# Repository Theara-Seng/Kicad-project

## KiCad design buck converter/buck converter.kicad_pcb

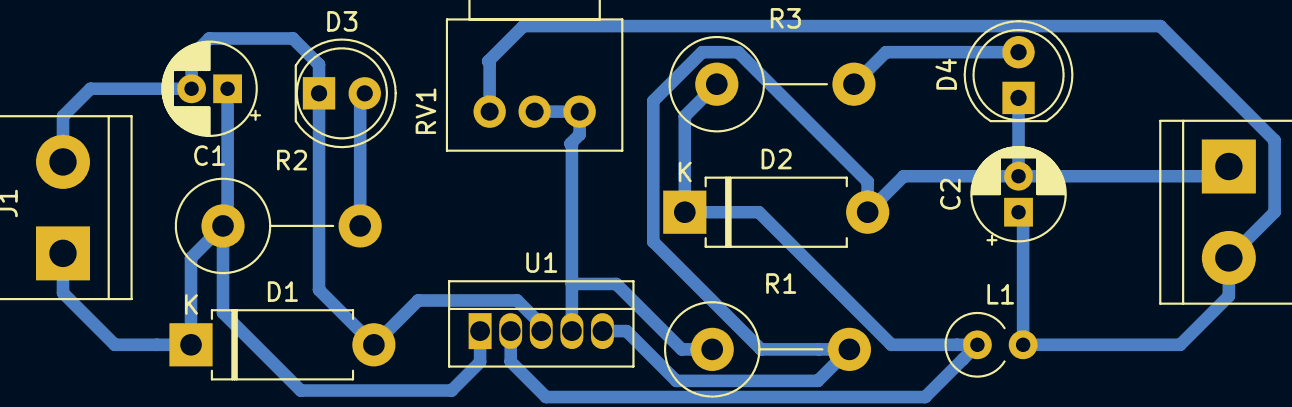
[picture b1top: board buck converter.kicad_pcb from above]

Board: 2 copper layers, 14 parts (0 on the bottom side), 7 nets.

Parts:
C1, C2: 220uF; CP_Radial_D5.0mm_P2.00mm
D1, D2: D_Schottky; D_DO-15_P10.16mm_Horizontal
D3, D4: LED; LED_D5.0mm
J1: Input; TerminalBlock_bornier-2_P5.08mm
J2: Output; TerminalBlock_bornier-2_P5.08mm
L1: L; L_Axial_L7.0mm_D3.3mm_P2.54mm_Vertical_Fastron_MICC
R1: 470; R_Axial_DIN0516_L15.5mm_D5.0mm_P7.62mm_Vertical
R2, R3: 1k; R_Axial_DIN0516_L15.5mm_D5.0mm_P7.62mm_Vertical
RV1: 10K; Potentiometer_Alps_RK097_Single_Horizontal
U1: LM2596S-ADJ; TO-262-5_Vertical

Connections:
GND: C1.2, C2.2, D1.2, D2.2, D3.1, D4.1, J1.2, J2.1, R1.2, U1.3, U1.5
unnamed: C1.1, D1.1, J1.1, R2.1, U1.1
unnamed: C2.1, J2.2, L1.2, RV1.3
unnamed: D2.1, L1.1, R3.1, U1.2
unnamed: D3.2, R2.2
unnamed: D4.2, R3.2
unnamed: R1.1, RV1.1, RV1.2, U1.4

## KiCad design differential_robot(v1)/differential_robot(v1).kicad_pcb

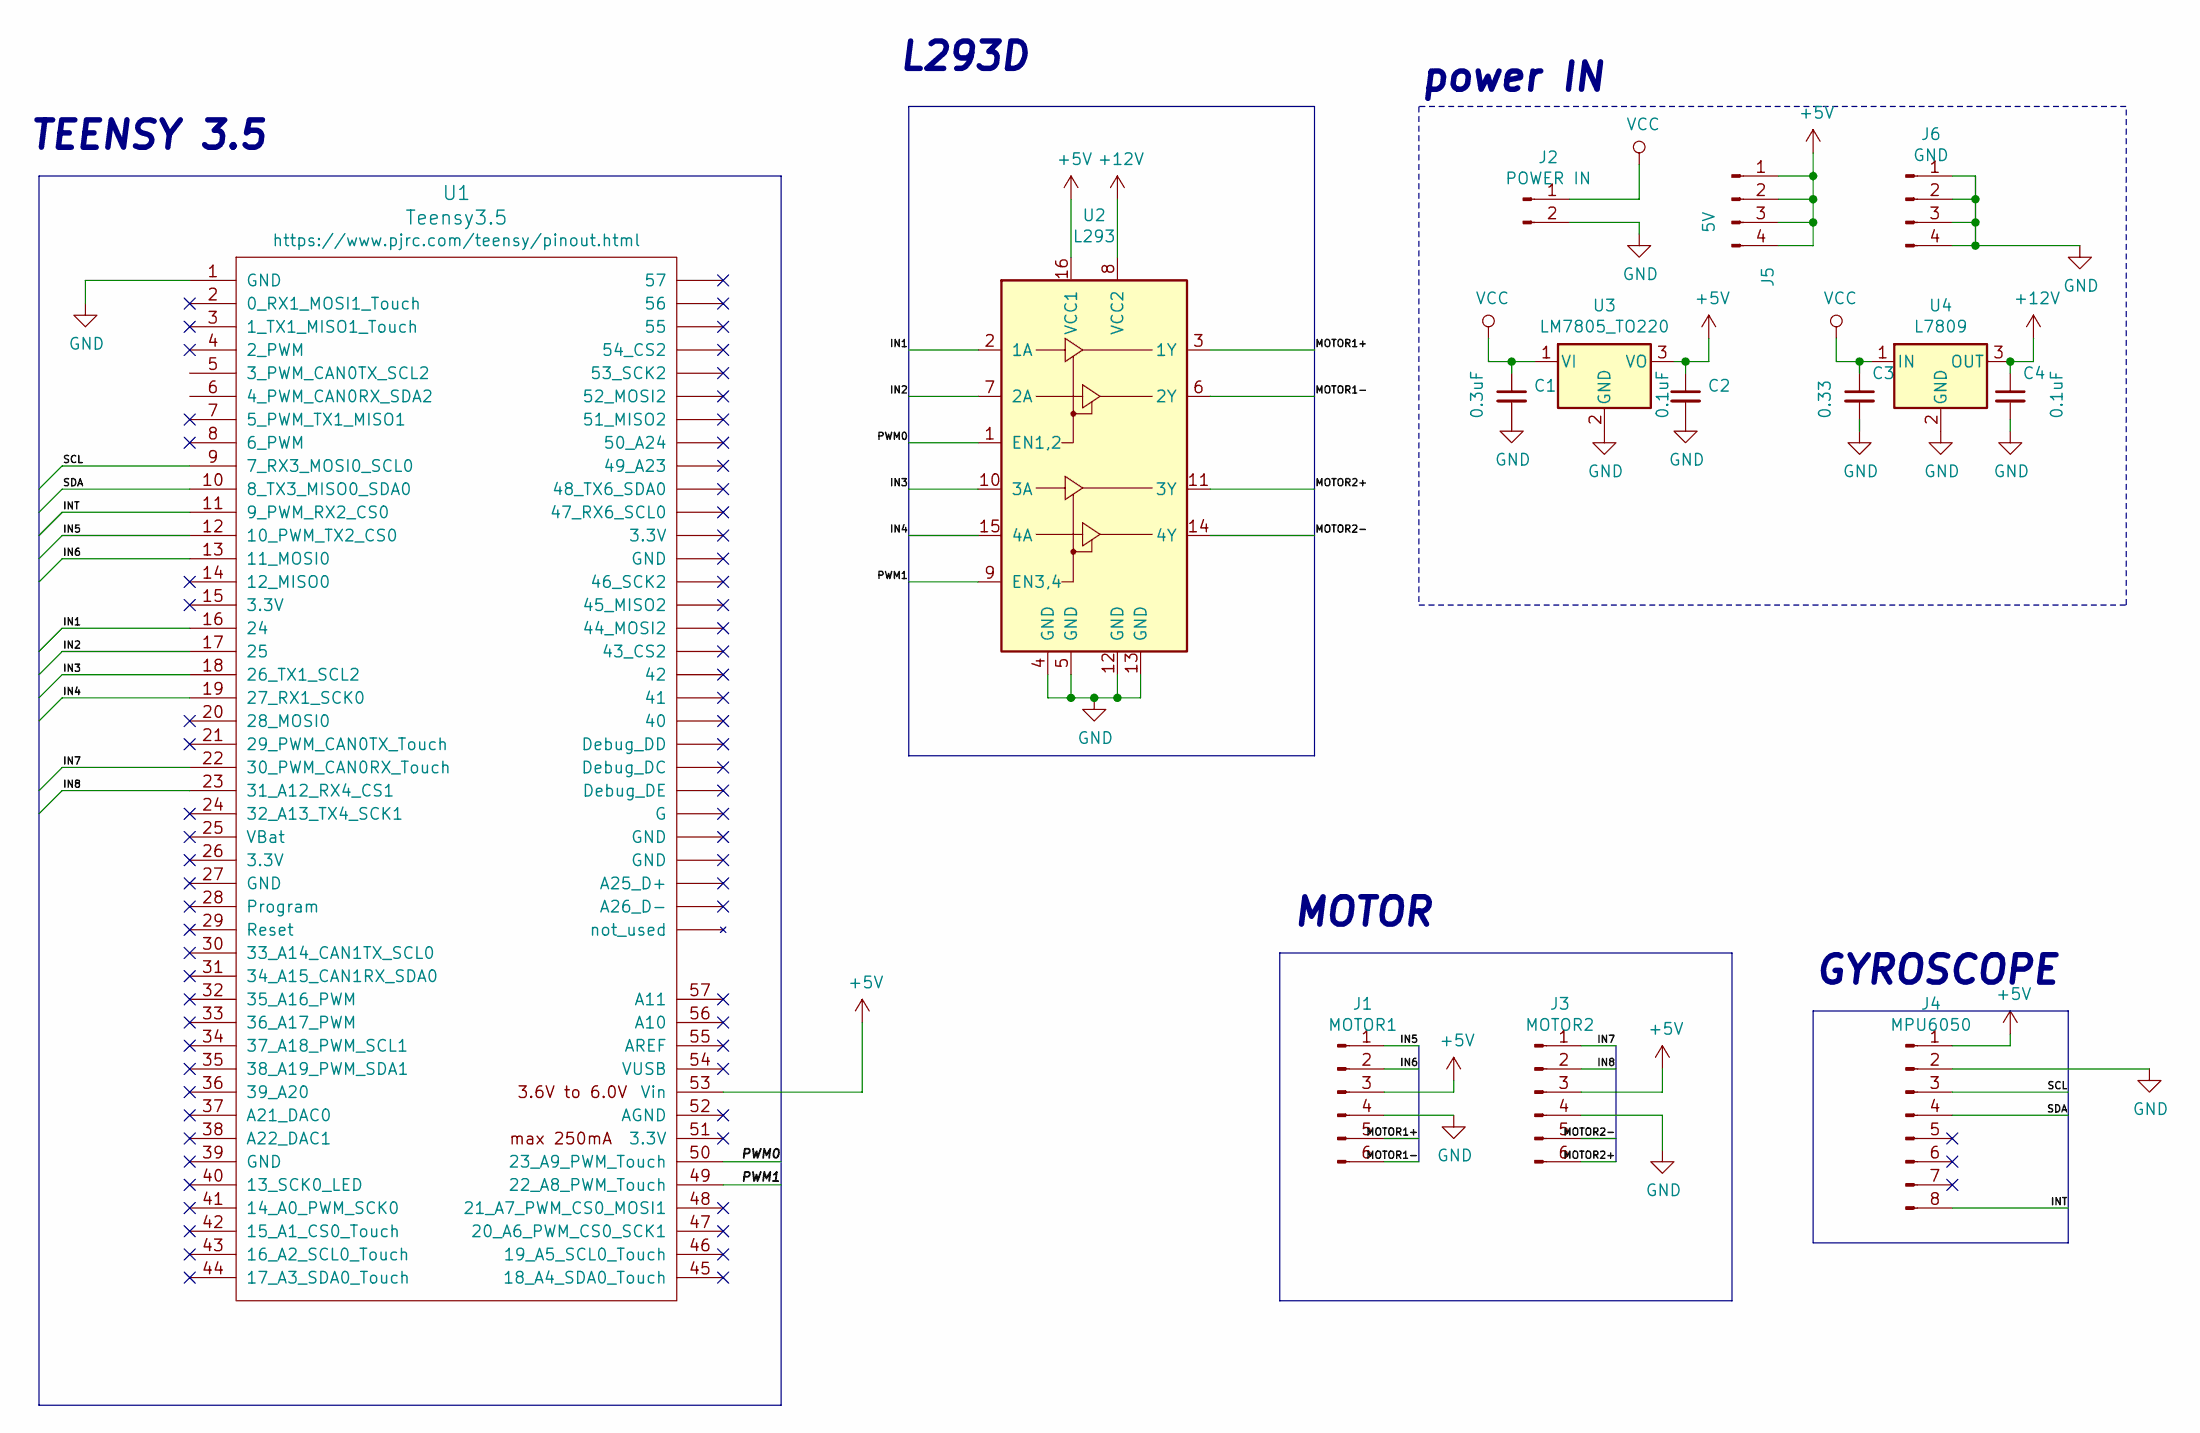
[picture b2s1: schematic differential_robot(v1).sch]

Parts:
C1: 0.3uF; CP_Radial_Tantal_D4.5mm_P2.50mm
C2, C4: 0.1uF; CP_Radial_Tantal_D4.5mm_P2.50mm
C3: 0.33; CP_Radial_Tantal_D4.5mm_P2.50mm
J1: MOTOR1; PinSocket_1x06_P2.54mm_Vertical
J2: POWER IN; TerminalBlock_bornier-2_P5.08mm
J3: MOTOR2; PinSocket_1x06_P2.54mm_Vertical
J4: MPU6050; PinSocket_1x08_P2.54mm_Vertical
J5: 5V; PinSocket_1x04_P2.54mm_Vertical
J6: GND; PinSocket_1x04_P2.54mm_Vertical
U1: Teensy3.5; Teensy35_36
U2: L293; DIP-16_W7.62mm
U3: LM7805_TO220; TO220
U4: L7809; TO220

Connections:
+5V: C2.1, J1.3, J3.3, J4.1, J5.1, J5.2, J5.3, J5.4, U1.53 (Vin), U2.16 (VCC1), U3.3 (VO)
+12V: C4.1, U2.8 (VCC2), U4.3 (OUT)
/IN1: U1.16 (24), U2.2 (1A)
/IN2: U1.17 (25), U2.7 (2A)
/IN3: U1.18 (26_TX1_SCL2), U2.10 (3A)
/IN4: U1.19 (27_RX1_SCK0), U2.15 (4A)
/IN5: J1.1, U1.12 (10_PWM_TX2_CS0)
/IN6: J1.2, U1.13 (11_MOSI0)
/IN7: J3.1, U1.22 (30_PWM_CAN0RX_Touch)
/IN8: J3.2, U1.23 (31_A12_RX4_CS1)
/INT: J4.8, U1.11 (9_PWM_RX2_CS0)
/MOTOR1+: J1.5, U2.3 (1Y)
/MOTOR1-: J1.6, U2.6 (2Y)
/MOTOR2+: J3.6, U2.11 (3Y)
/MOTOR2-: J3.5, U2.14 (4Y)
/PWM0: U1.50 (23_A9_PWM_Touch), U2.1 (EN1,2)
/PWM1: U1.49 (22_A8_PWM_Touch), U2.9 (EN3,4)
/SCL: J4.3, U1.9 (7_RX3_MOSI0_SCL0)
/SDA: J4.4, U1.10 (8_TX3_MISO0_SDA0)
GND: C1.2, C2.2, C3.2, C4.2, J1.4, J2.2, J3.4, J4.2, J6.1, J6.2, J6.3, J6.4, U1.1 (GND), U2.4 (GND), U2.5 (GND), U2.12 (GND), U2.13 (GND), U3.2 (GND), U4.2 (GND)
VCC: C1.1, C3.1, J2.1, U3.1 (VI), U4.1 (IN)

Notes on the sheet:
power IN
MOTOR
GYROSCOPE
L293D
TEENSY 3.5

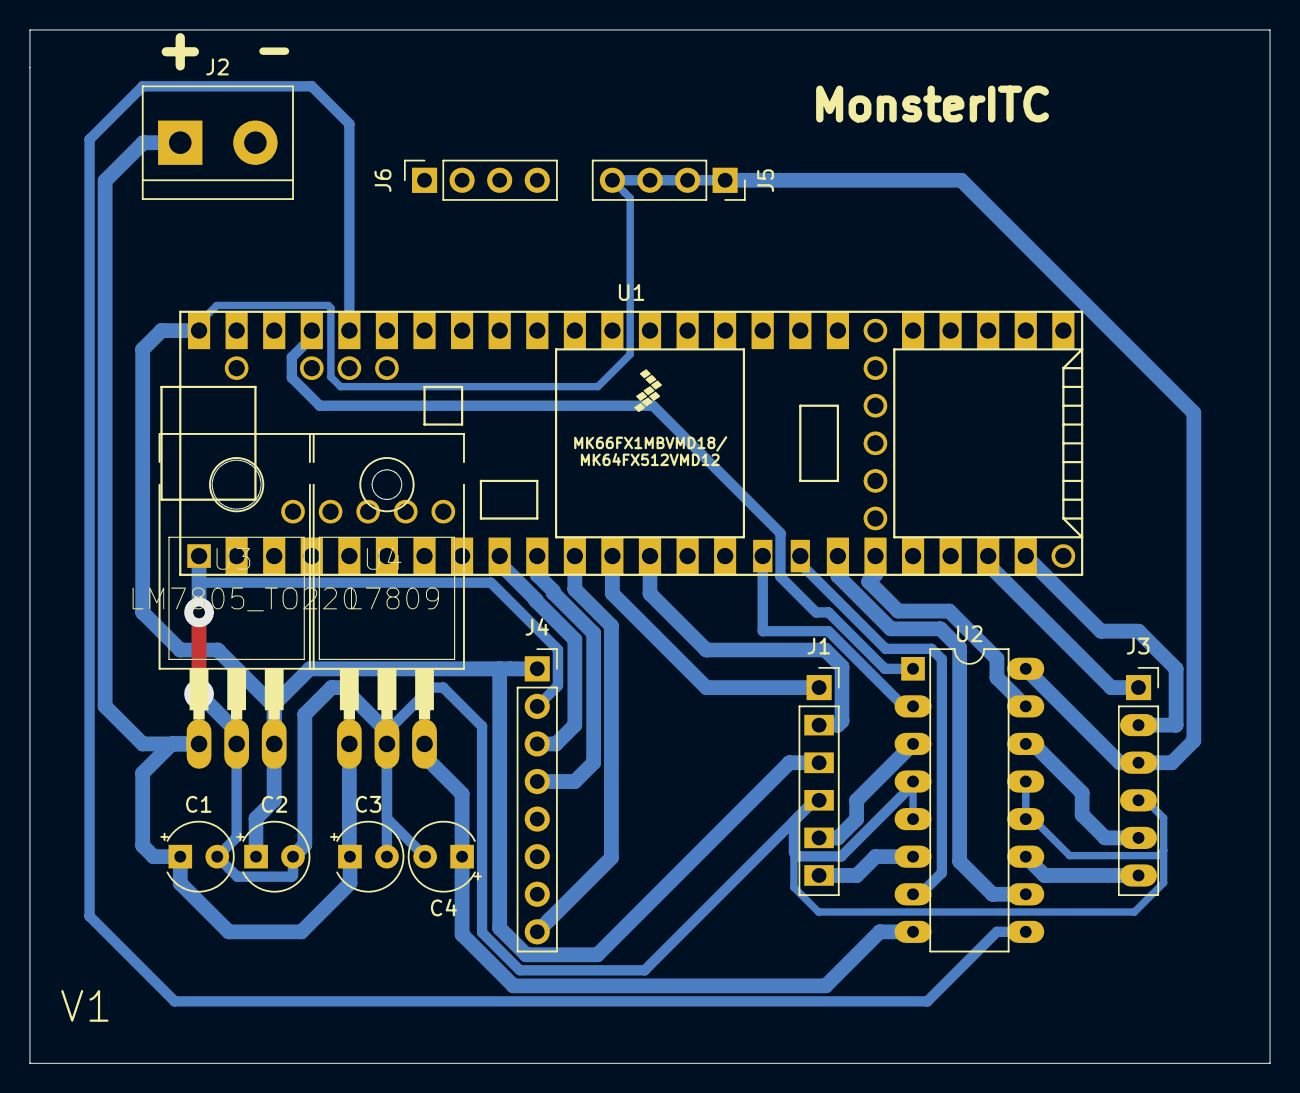
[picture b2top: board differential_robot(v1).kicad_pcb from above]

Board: 2 copper layers, 83.8 x 69.8 mm, 14 parts (0 on the bottom side), 21 nets.

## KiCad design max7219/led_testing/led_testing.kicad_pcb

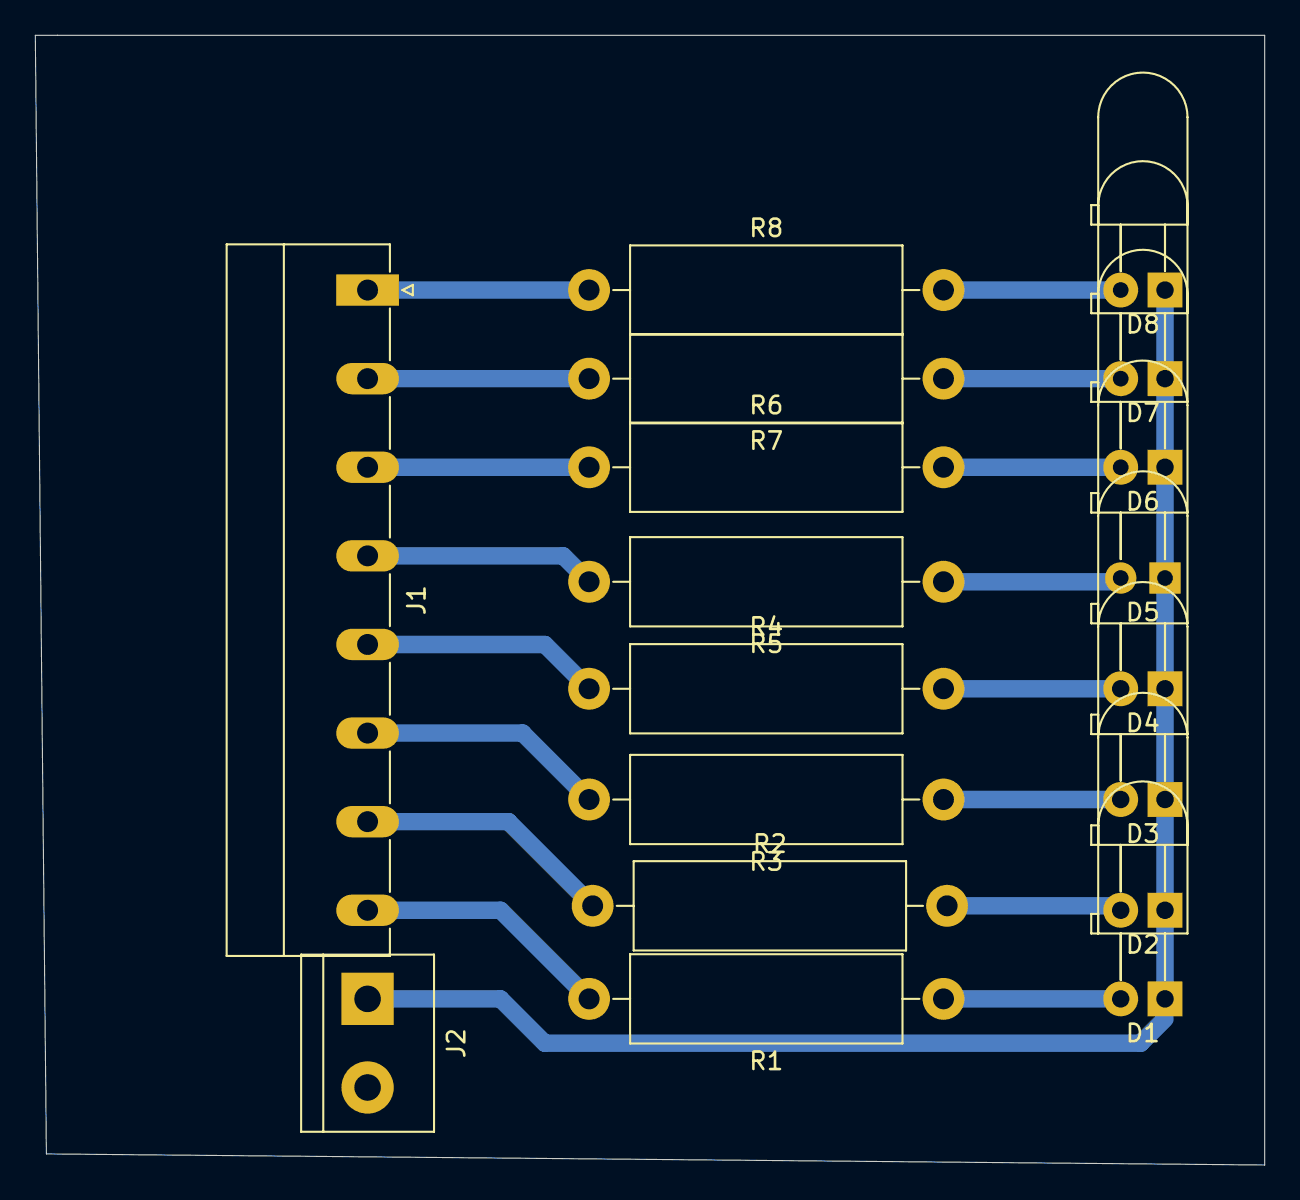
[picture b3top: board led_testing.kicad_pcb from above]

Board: 2 copper layers, 70.5 x 64.8 mm, 18 parts (0 on the bottom side), 17 nets.

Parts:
D1, D2, D3, D4, D5, D6, D7, D8: LED; LED_D5.0mm_Horizontal_O3.81mm_Z15.0mm
J1: Conn_01x08_Female; PhoenixContact_MC-G_08x5.08mm_Angled
J2: Conn_01x01_Female; TerminalBlock_bornier-2_P5.08mm
R1, R2, R3, R4, R5, R6, R7, R8: R; R_Axial_DIN0516_L15.5mm_D5.0mm_P20.32mm_Horizontal

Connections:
/GND: D1.1, D2.1, D3.1, D4.1, D5.1, D6.1, D7.1, D8.1, J2.1
/PB0: J1.8, R1.2
/PB1: J1.7, R2.1
/PB2: J1.6, R3.2
/PB3: J1.5, R4.1
/PB4: J1.4, R5.2
/PB5: J1.3, R6.1
/PB6: J1.2, R7.2
/PB7: J1.1, R8.1
unnamed: D1.2, R1.1
unnamed: D2.2, R2.2
unnamed: D3.2, R3.1
unnamed: D4.2, R4.2
unnamed: D5.2, R5.1
unnamed: D6.2, R6.2
unnamed: D7.2, R7.1
unnamed: D8.2, R8.2

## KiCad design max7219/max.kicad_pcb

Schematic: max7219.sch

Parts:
C1: C; CP_Radial_D13.0mm_P5.00mm
C2: C; CP_Radial_D14.0mm_P5.00mm
D1, D2, D3, D4, D5, D6, D7, D8, D9, D10, D11, D12, D13, D14, D15, D16, D17, D18, D19, D20, D21, D22, D23, D24, D25, D26, D27, D28, D29, D30, D31, D32, D33, D34, D35, D36, D37, D38, D39, D40, D41, D42, D43, D44, D45, D46, D47, D48, D49, D50, D51, D52, D53, D54, D55, D56, D57, D58, D59, D60, D61, D62, D63, D64: LED; LED_D3.0mm_Horizontal_O1.27mm_Z2.0mm
J1: Conn_01x05_Female; TerminalBlock_bornier-5_P5.08mm
R1: R; R_Axial_DIN0614_L14.3mm_D5.7mm_P15.24mm_Horizontal
U1: MAX7219; DIL24

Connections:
CLK: J1.2, U1.13
DIG0: D1.1 (K), D9.1 (K), D17.1 (K), D25.1 (K), D33.1 (K), D41.1 (K), D49.1 (K), D57.1 (K), U1.2
DIG1: D2.1 (K), D10.1 (K), D18.1 (K), D26.1 (K), D34.1 (K), D42.1 (K), D50.1 (K), D58.1 (K), U1.11
DIG2: D3.1 (K), D11.1 (K), D19.1 (K), D27.1 (K), D35.1 (K), D43.1 (K), D51.1 (K), D59.1 (K), U1.6
DIG3: D4.1 (K), D12.1 (K), D20.1 (K), D28.1 (K), D36.1 (K), D44.1 (K), D52.1 (K), D60.1 (K), U1.7
DIG4: D5.1 (K), D13.1 (K), D21.1 (K), D29.1 (K), D37.1 (K), D45.1 (K), D53.1 (K), D61.1 (K), U1.3
DIG5: D6.1 (K), D14.1 (K), D22.1 (K), D30.1 (K), D38.1 (K), D46.1 (K), D54.1 (K), D62.1 (K), U1.10
DIG6: D7.1 (K), D15.1 (K), D23.1 (K), D31.1 (K), D39.1 (K), D47.1 (K), D55.1 (K), D63.1 (K), U1.5
DIG7: D8.1 (K), D16.1 (K), D24.1 (K), D32.1 (K), D40.1 (K), D48.1 (K), D56.1 (K), D64.1 (K), U1.8
DIN: J1.4, U1.1
GND: C1.1, C2.1, J1.1, U1.4, U1.9
LOAD: J1.3, U1.12
unnamed: R1.2, U1.18
SEGA: D9.2 (A), D10.2 (A), D11.2 (A), D12.2 (A), D13.2 (A), D14.2 (A), D15.2 (A), D16.2 (A), U1.14
SEGB: D17.2 (A), D18.2 (A), D19.2 (A), D20.2 (A), D21.2 (A), D22.2 (A), D23.2 (A), D24.2 (A), U1.16
SEGC: D25.2 (A), D26.2 (A), D27.2 (A), D28.2 (A), D29.2 (A), D30.2 (A), D31.2 (A), D32.2 (A), U1.20
SEGD: D33.2 (A), D34.2 (A), D35.2 (A), D36.2 (A), D37.2 (A), D38.2 (A), D39.2 (A), D40.2 (A), U1.23
SEGDP: D1.2 (A), D2.2 (A), D3.2 (A), D4.2 (A), D5.2 (A), D6.2 (A), D7.2 (A), D8.2 (A), U1.22
SEGE: D41.2 (A), D42.2 (A), D43.2 (A), D44.2 (A), D45.2 (A), D46.2 (A), D47.2 (A), D48.2 (A), U1.21
SEGF: D49.2 (A), D50.2 (A), D51.2 (A), D52.2 (A), D53.2 (A), D54.2 (A), D55.2 (A), D56.2 (A), U1.15
SEGG: D57.2 (A), D58.2 (A), D59.2 (A), D60.2 (A), D61.2 (A), D62.2 (A), D63.2 (A), D64.2 (A), U1.17
VCC: C1.2, C2.2, J1.5, R1.1, U1.19

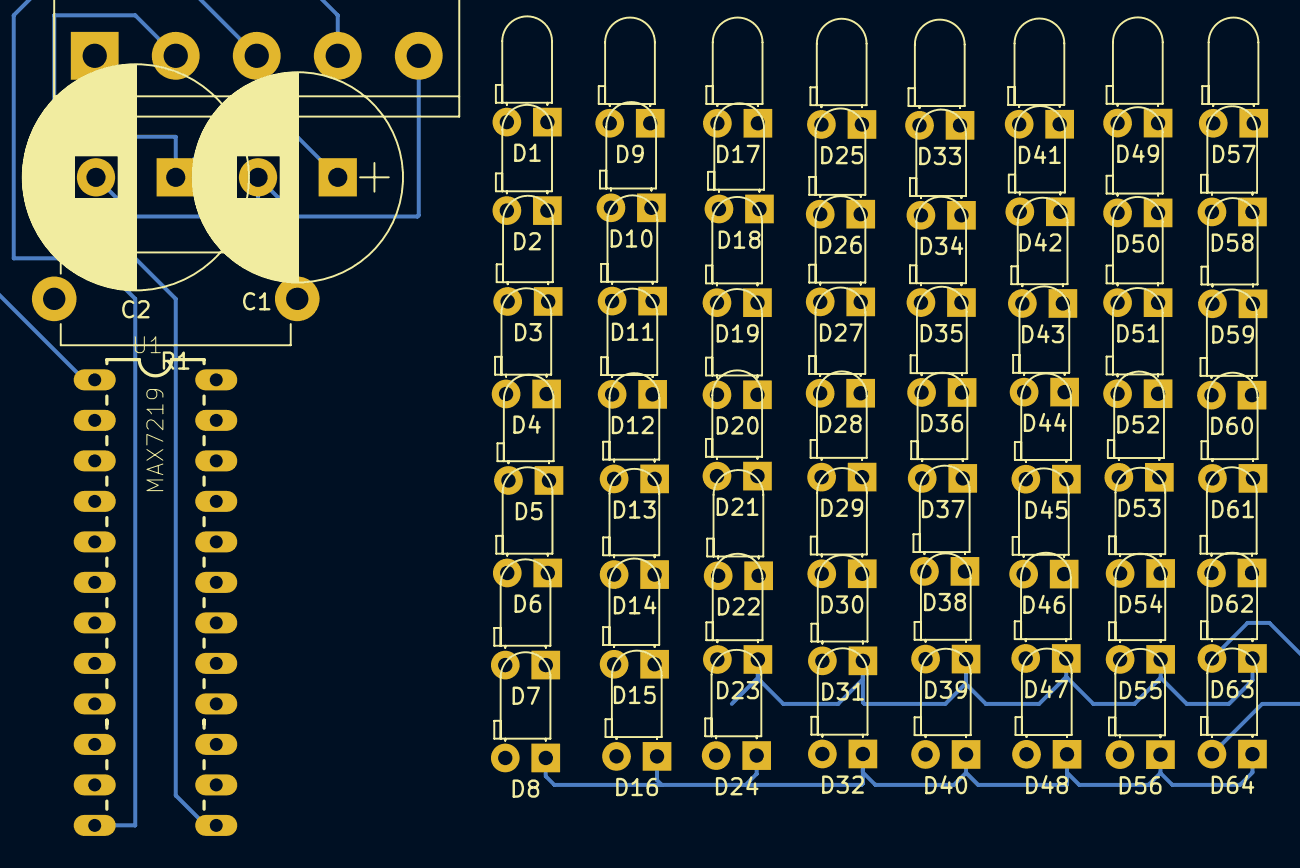
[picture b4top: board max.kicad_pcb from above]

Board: 2 copper layers, 69 parts (0 on the bottom side), 22 nets.

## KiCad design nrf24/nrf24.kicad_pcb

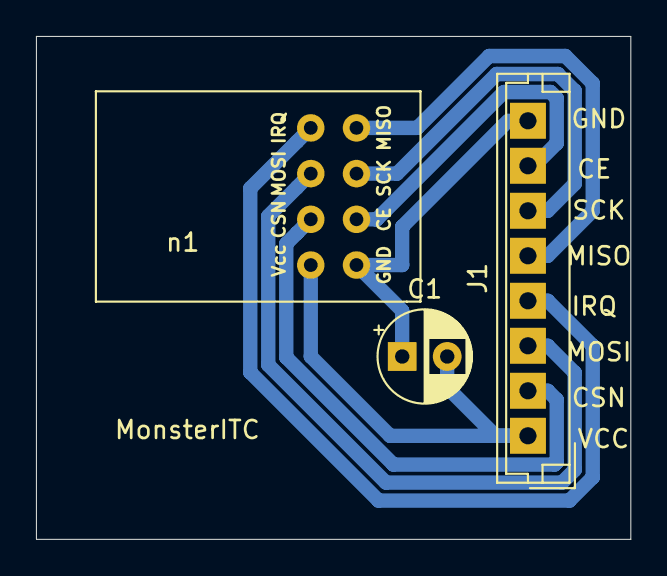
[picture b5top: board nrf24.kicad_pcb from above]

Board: 2 copper layers, 33.0 x 27.9 mm, 3 parts (0 on the bottom side), 8 nets.

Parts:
C1: C; CP_Radial_D5.0mm_P2.50mm
J1: C; JST_EH_B8B-EH-A_1x08_P2.50mm_Vertical
n1: nrf24

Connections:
unnamed: C1.1, J1.8, n1.0
unnamed: C1.2, J1.1, n1.7
unnamed: J1.2, n1.6
unnamed: J1.3, n1.5
unnamed: J1.4, n1.4
unnamed: J1.5, n1.3
unnamed: J1.6, n1.2
unnamed: J1.7, n1.1

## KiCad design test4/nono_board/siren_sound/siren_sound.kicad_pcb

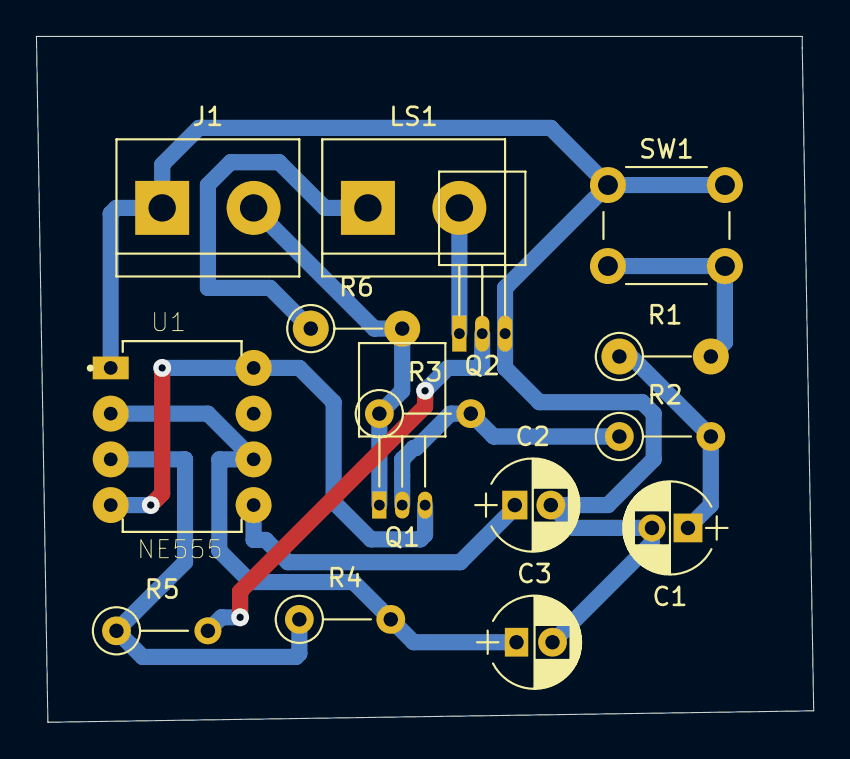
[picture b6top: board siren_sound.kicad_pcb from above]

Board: 2 copper layers, 43.2 x 38.1 mm, 15 parts (0 on the bottom side), 12 nets.

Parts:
C1, C2, C3: C; CP_Radial_D5.0mm_P2.00mm
J1: Conn_01x02_Female; TerminalBlock_bornier-2_P5.08mm
LS1: Speaker; TerminalBlock_bornier-2_P5.08mm
Q1, Q2: BC546; TO-92_Horizontal2_Inline_Narrow_Oval
R1, R2, R3, R4, R5, R6: R; R_Axial_DIN0207_L6.3mm_D2.5mm_P5.08mm_Vertical
SW1: SW_Push_Dual; SW_PUSH_6mm
U1: NE555; DIP794W45P254L1060H508Q8

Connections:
unnamed: C1.1, R1.1, R2.2
unnamed: C1.2, C2.2, C3.2, J1.1, Q2.3, SW1.1, U1.1
unnamed: C2.1, U1.5
unnamed: C3.1, R4.2, U1.2, U1.6
unnamed: LS1.1, R6.1
unnamed: LS1.2, Q2.1
unnamed: Q1.2, R2.1, R3.2
unnamed: Q2.2, R5.2
unnamed: R1.2, SW1.2
unnamed: R4.1, R5.1, U1.3
V: Q1.3, U1.4, U1.8
Vcc: J1.2, Q1.1, R3.1, R6.2
